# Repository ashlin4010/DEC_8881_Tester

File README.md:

# DEC_8881_Tester
A simple tester for DEC 8881 chips.

## Usage ##
 1. Plug it into 5 volt power centre positive power.
 2. Install chip
 3. Press Buttons

## Bill of materials ##

| Quantity | Part | Link |
|:---:|:---:|:---:|
| 5 | 1K Resistor |  |
| 8 | 10K Resistor |  |
| 8 | Push Button | https://www.digikey.co.nz/en/products/detail/same-sky-formerly-cui-devices/TS02-66-70-BK-160-LCR-D/15634243 |
| 1 | Barrel Jack | https://www.digikey.co.nz/en/products/detail/same-sky-formerly-cui-devices/PJ-037A/1644545 |
| 1 | DIP-14 ZIF Socket | https://www.aliexpress.com/item/1005007048855354.html |
| 1 | 74HCT541 | https://www.digikey.co.nz/en/products/detail/texas-instruments/SN74HCT541N/277265 |
| 1 | 390ohm Bussed | https://www.digikey.co.nz/en/products/detail/bourns-inc/4606X-101-391LF/1088986 |
| 1 | 180ohm Bussed | https://www.digikey.co.nz/en/products/detail/bourns-inc/4606X-101-181LF/1088969 |
| 5 | 3mm LED RED |  |

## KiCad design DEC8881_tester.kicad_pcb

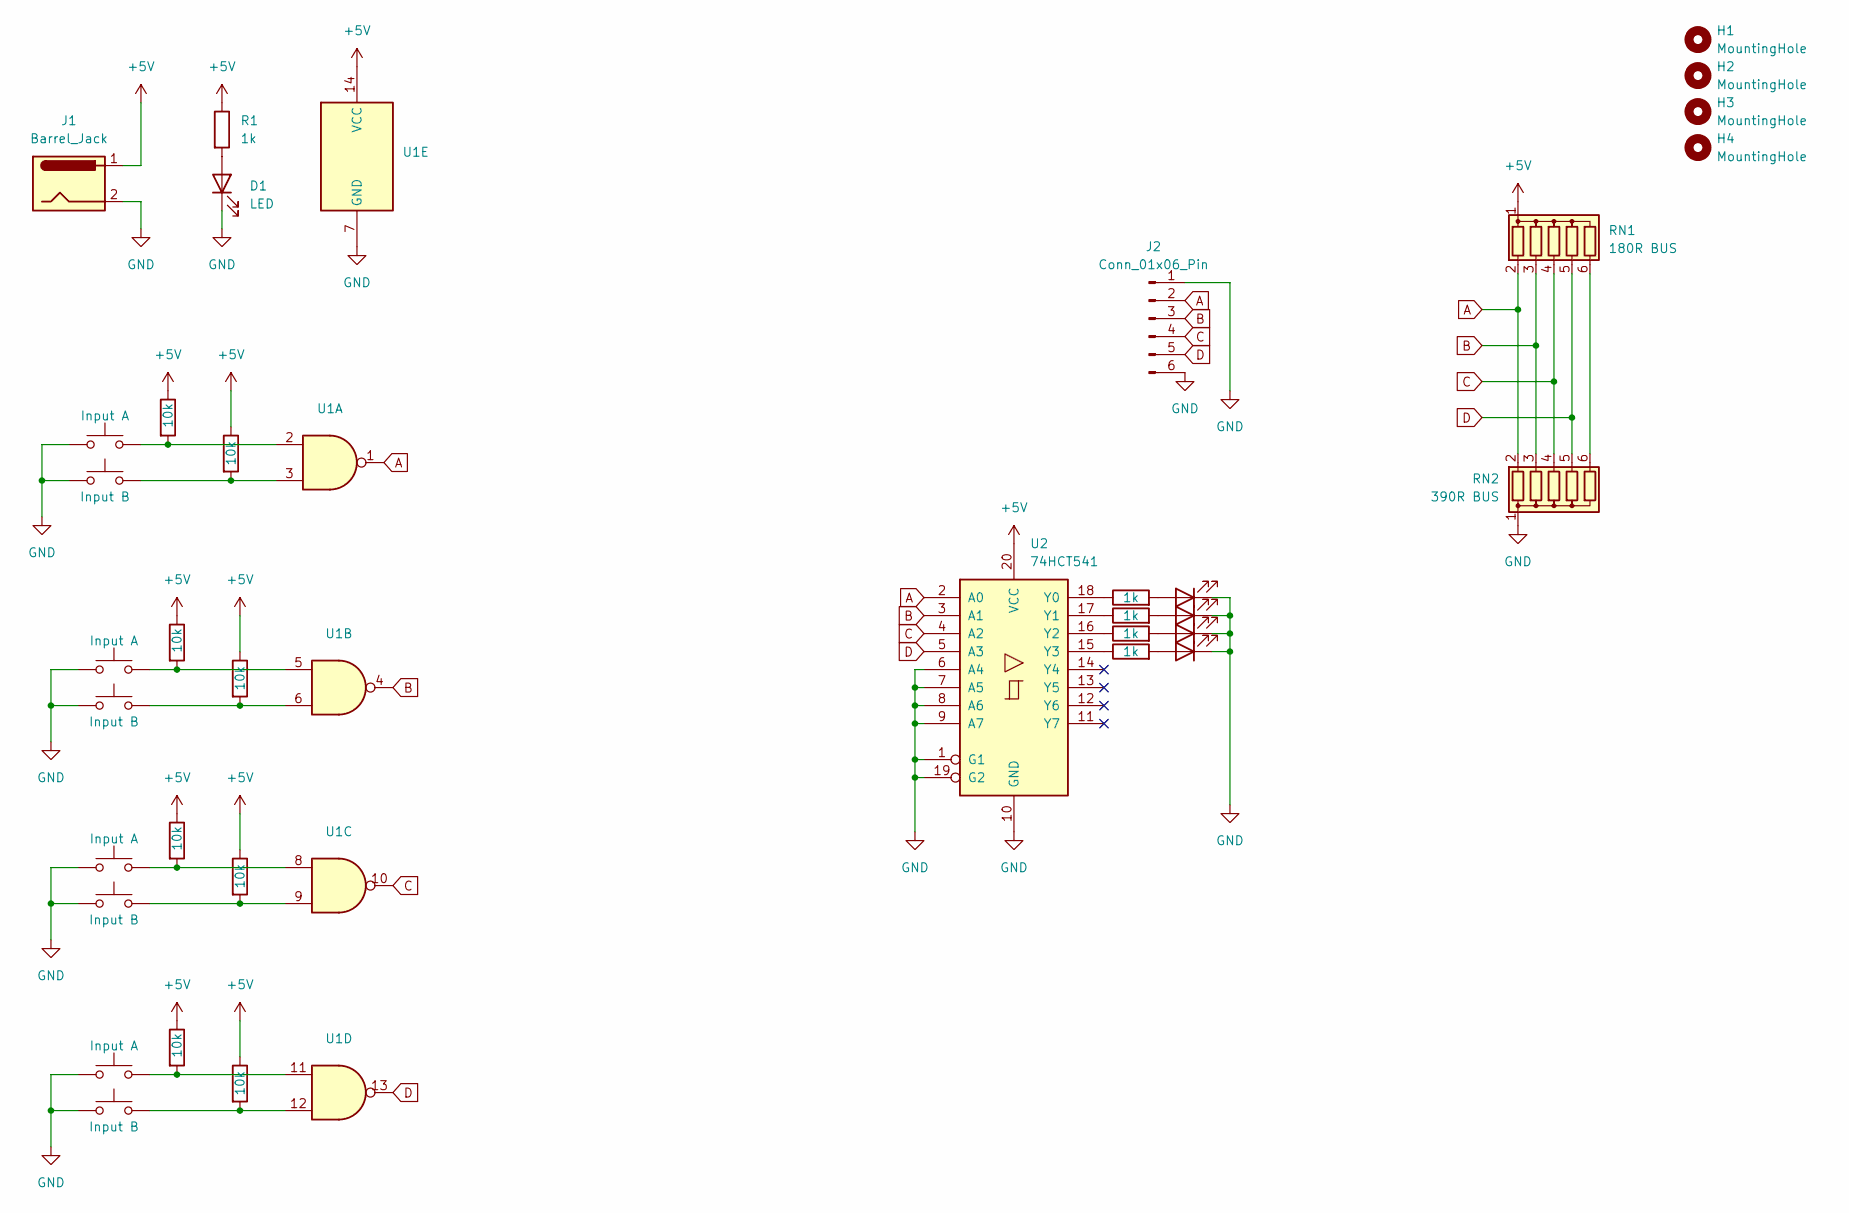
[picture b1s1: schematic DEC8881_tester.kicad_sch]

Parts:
D1, D2, D3, D4, D5: LED; LED_D3.0mm
H1, H2, H3, H4: MountingHole; MountingHole_3.2mm_M3
J1: Barrel_Jack; BarrelJack_GCT_DCJ200-10-A_Horizontal
J2: Conn_01x06_Pin; PinHeader_1x06_P2.54mm_Vertical
R1, R10, R11, R12, R13: 1k; R_Axial_DIN0204_L3.6mm_D1.6mm_P7.62mm_Horizontal
R2, R3, R4, R5, R6, R7, R8, R9: 10k; R_Axial_DIN0204_L3.6mm_D1.6mm_P7.62mm_Horizontal
RN1: 180R BUS; R_Array_SIP6
RN2: 390R BUS; R_Array_SIP6
SW1, SW3, SW5, SW7: Input A; SW_PUSH_6mm_H4.3mm
SW2, SW4, SW6, SW8: Input B; SW_PUSH_6mm_H4.3mm
U1: DIP_Socket-14_W4.3_W5.08_W7.62_W10.16_W10.9_3M_214-3339-00-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
U2: 74HCT541; DIP-20_W7.62mm

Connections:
+5V: J1.1, R1.1, R2.1, R3.1, R4.1, R5.1, R6.1, R7.1, R8.1, R9.1, RN1.1 (common), U1.14 (VCC), U2.20 (VCC)
A: J2.2, RN1.2 (R1), RN2.2 (R1), U1.1, U2.2 (A0)
B: J2.3, RN1.3 (R2), RN2.3 (R2), U1.4, U2.3 (A1)
C: J2.4, RN1.4 (R3), RN2.4 (R3), U1.10, U2.4 (A2)
D: J2.5, RN1.5 (R4), RN2.5 (R4), U1.13, U2.5 (A3)
GND: D1.1 (K), D2.1 (K), D3.1 (K), D4.1 (K), D5.1 (K), J1.2, J2.1, J2.6, RN2.1 (common), SW1.1, SW2.1, SW3.1, SW4.1, SW5.1, SW6.1, SW7.1, SW8.1, U1.7 (GND), U2.1 (G1), U2.6 (A4), U2.7 (A5), U2.8 (A6), U2.9 (A7), U2.10 (GND), U2.19 (G2)
unnamed: D1.2 (A), R1.2
unnamed: D2.2 (A), R10.2
unnamed: D3.2 (A), R11.2
unnamed: D4.2 (A), R12.2
unnamed: D5.2 (A), R13.2
unnamed: R2.2, SW1.2, U1.2
unnamed: R3.2, SW2.2, U1.3
unnamed: R4.2, SW3.2, U1.5
unnamed: R5.2, SW4.2, U1.6
unnamed: R6.2, SW5.2, U1.8
unnamed: R7.2, SW6.2, U1.9
unnamed: R8.2, SW7.2, U1.11
unnamed: R9.2, SW8.2, U1.12
unnamed: RN1.6 (R5), RN2.6 (R5)
unnamed: R10.1, U2.18 (Y0)
unnamed: R11.1, U2.17 (Y1)
unnamed: R12.1, U2.16 (Y2)
unnamed: R13.1, U2.15 (Y3)

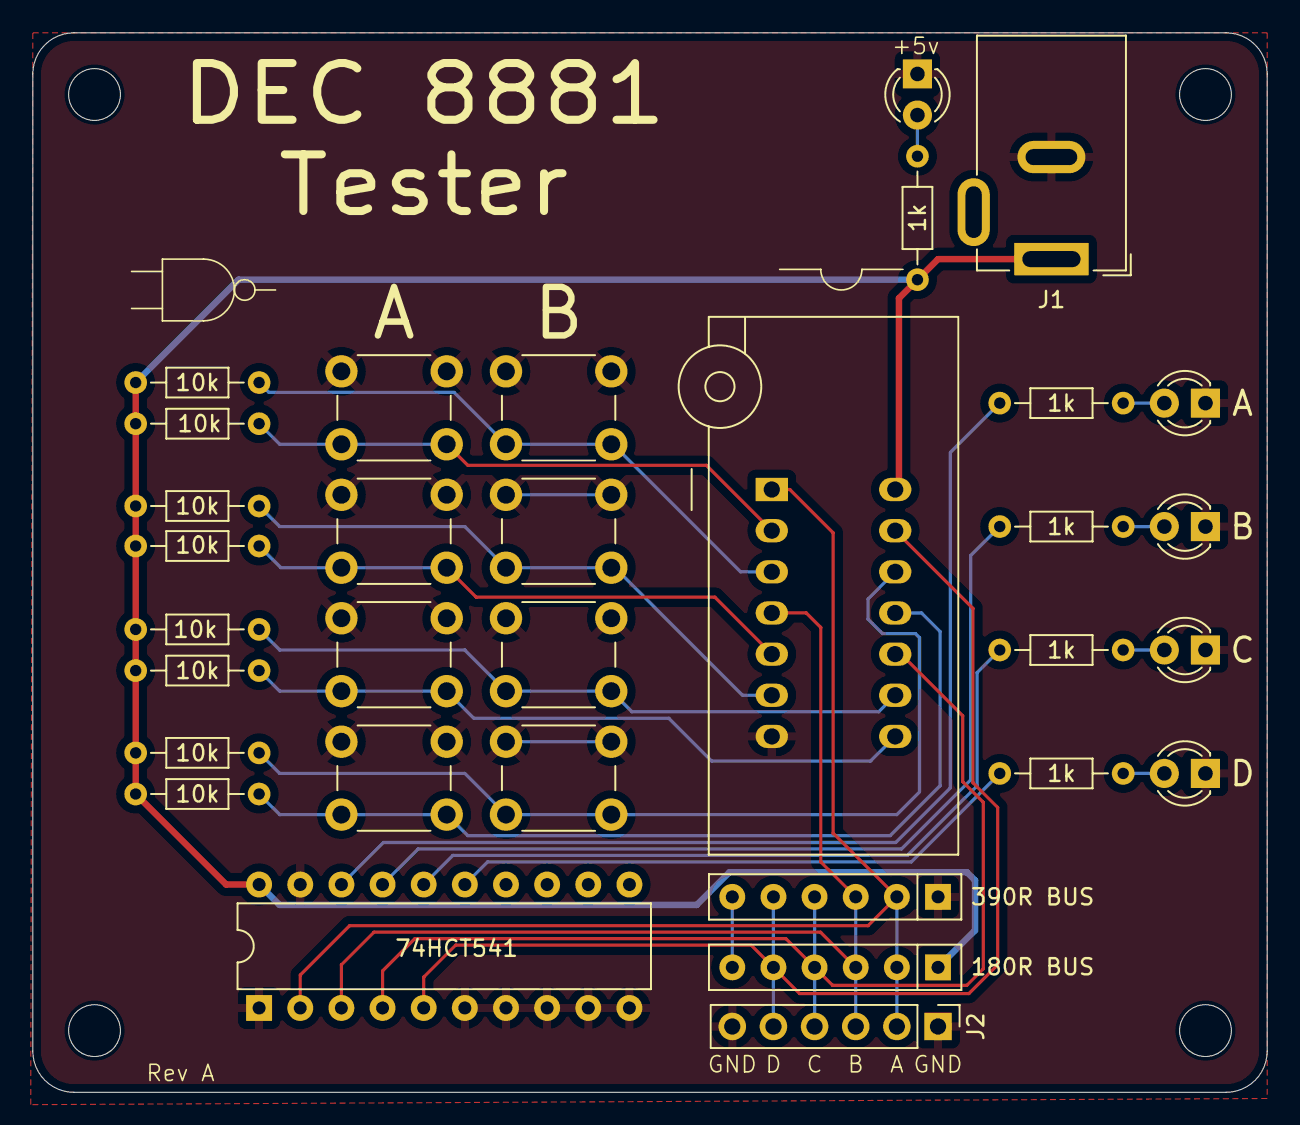
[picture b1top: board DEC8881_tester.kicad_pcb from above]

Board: 2 copper layers, 76.2 x 65.4 mm, 36 parts (0 on the bottom side), 24 nets.

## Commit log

2024-11-19 Added PCB files
2024-12-06 Added image and new manufacturer files
2024-12-06 Fix BOM
